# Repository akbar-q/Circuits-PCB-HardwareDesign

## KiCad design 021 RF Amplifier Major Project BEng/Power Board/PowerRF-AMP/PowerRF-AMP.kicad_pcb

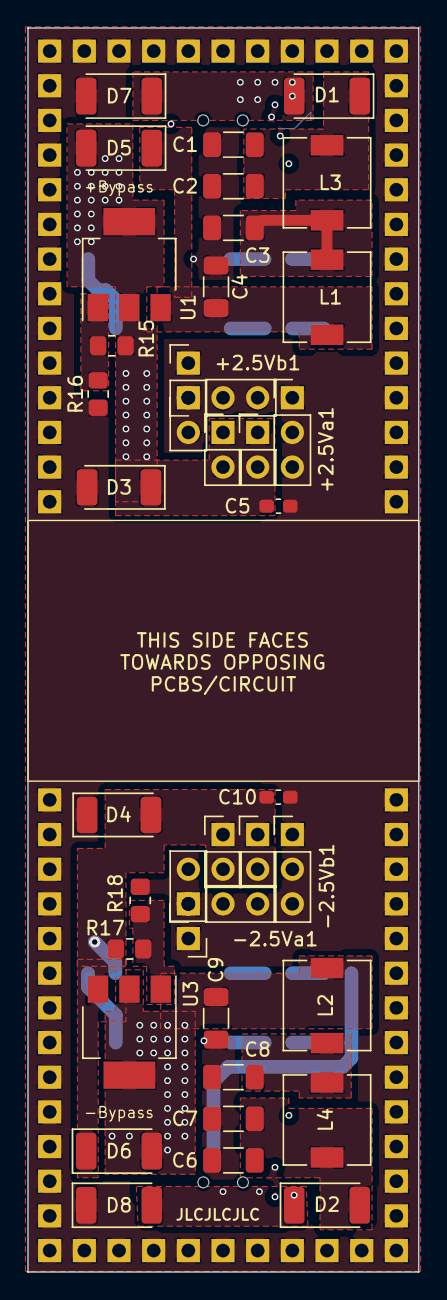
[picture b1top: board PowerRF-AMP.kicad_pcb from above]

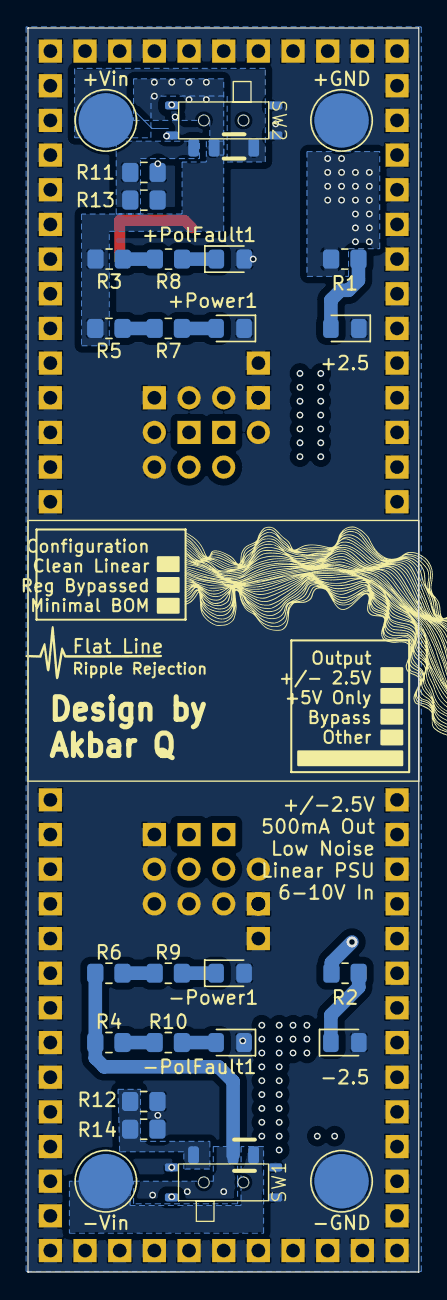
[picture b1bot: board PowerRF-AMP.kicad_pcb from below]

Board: 4 copper layers, 28.6 x 91.1 mm, 64 parts (26 on the bottom side), 27 nets.

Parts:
+2.5: LED; LED_0805_2012Metric_Pad1.15x1.40mm_HandSolder
+2.5Va1, +2.5Vb1: Conn_01x02_Pin; PinHeader_1x02_P2.54mm_Vertical
+G1, +G2, +G3: Conn_01x03; PinHeader_1x03_P2.54mm_Vertical
+GND: TestPoint; TestPoint_Pad_D4.0mm
+PolFault1: LED; LED_0805_2012Metric_Pad1.15x1.40mm_HandSolder
+Power1: LED; LED_0805_2012Metric_Pad1.15x1.40mm_HandSolder
+Vin: TestPoint; TestPoint_Pad_D4.0mm
-2.5: LED; LED_0805_2012Metric_Pad1.15x1.40mm_HandSolder
-2.5Va1, -2.5Vb1: Conn_01x02_Pin; PinHeader_1x02_P2.54mm_Vertical
-G1, -G2, -G3: Conn_01x03; PinHeader_1x03_P2.54mm_Vertical
-GND: TestPoint; TestPoint_Pad_D4.0mm
-PolFault1: LED; LED_0805_2012Metric_Pad1.15x1.40mm_HandSolder
-Power1: LED; LED_0805_2012Metric_Pad1.15x1.40mm_HandSolder
-Vin: TestPoint; TestPoint_Pad_D4.0mm
C1, C2, C3, C4, C6, C7, C8, C9: 2.2u; C_1206_3216Metric_Pad1.33x1.80mm_HandSolder
C5, C10: 100n; C_0603_1608Metric_Pad1.08x0.95mm_HandSolder
D1, D2: Diode; D_MELF
D3, D4: D_Zener; D_2010_5025Metric_Pad1.52x2.65mm_HandSolder
D5, D6: Bypass; D_MELF
D7, D8: PolFaultClamp-DNP; D_MELF
L1, L2, L3, L4: L; L_6.3x6.3_H3
R1, R2, R3, R4, R5, R6, R7, R8, R9, R10, R11, R12, R13, R14, R15, R16, R17, R18: 680R; R_0805_2012Metric_Pad1.20x1.40mm_HandSolder
SW1, SW2: SW_SPDT; SPDT-Long-SMD
U1: LM317_SOT-223; SOT-223-3_TabPin2
U3: LM337_SOT223; SOT-223-3_TabPin2

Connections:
GND: +2.5.1 (K), +G1.1, +G1.2, +G1.3, +G2.1, +G2.2, +G2.3, +G3.1, +G3.2, +G3.3, +GND.1, +PolFault1.2 (A), +Power1.1 (K), -2.5.2 (A), -G1.1, -G1.2, -G1.3, -G2.1, -G2.2, -G2.3, -G3.1, -G3.2, -G3.3, -GND.1, -PolFault1.1 (K), -Power1.2 (A), C1.2, C2.2, C3.2, C4.2, C5.2, C6.2, C7.2, C8.2, C9.2, C10.2, D3.2 (A), D4.1 (K), D7.2 (A), D8.1 (K), R11.2, R12.2, R13.2, R14.2, R16.1, R18.1, SW1.0, SW2.0
unnamed: +2.5.2 (A), R1.2
unnamed: +2.5Va1.1, +2.5Va1.2, +2.5Vb1.1, +2.5Vb1.2, C5.1, D3.1 (K), D5.2 (A), R1.1, R15.2, U1.2 (VO)
unnamed: +PolFault1.1 (K), R8.1
unnamed: +Power1.2 (A), R7.1
unnamed: -2.5.1 (K), R2.2
unnamed: -2.5Va1.1, -2.5Va1.2, -2.5Vb1.1, -2.5Vb1.2, C10.1, D4.2 (A), D6.1 (K), R2.1, R17.2, U3.3 (VO)
unnamed: -PolFault1.2 (A), R10.1
unnamed: -Power1.1 (K), R9.1
unnamed: C3.1, L1.1, L3.2
unnamed: C8.1, L2.1, L4.2
unnamed: D1.2 (A), D7.1 (K), R3.2, R5.2, SW2.2 (B)
unnamed: C1.1, C2.1, D1.1 (K), L3.1
unnamed: C6.1, C7.1, D2.2 (A), L4.1
unnamed: D2.1 (K), D8.2 (A), R4.2, R6.2, SW1.2 (B)
unnamed: C4.1, D5.1 (K), L1.2, U1.3 (VI)
unnamed: C9.1, D6.2 (A), L2.2, U3.2 (VI)
unnamed: R3.1, R8.2
unnamed: R5.1, R7.2
unnamed: R6.1, R9.2
unnamed: R4.1, R10.2
unnamed: R12.1, R14.1, SW1.1 (A)
unnamed: -Vin.1, SW1.3 (C)
unnamed: +Vin.1, SW2.1 (A)
unnamed: R11.1, R13.1, SW2.3 (C)
unnamed: R15.1, R16.2, U1.1 (ADJ)
unnamed: R17.1, R18.2, U3.1 (ADJ)

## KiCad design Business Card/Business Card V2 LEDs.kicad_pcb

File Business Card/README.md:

## ADD QR CODES TO CONTACT BASED ON WEBSITE REDACTED INFORMATION AND WEBLINK

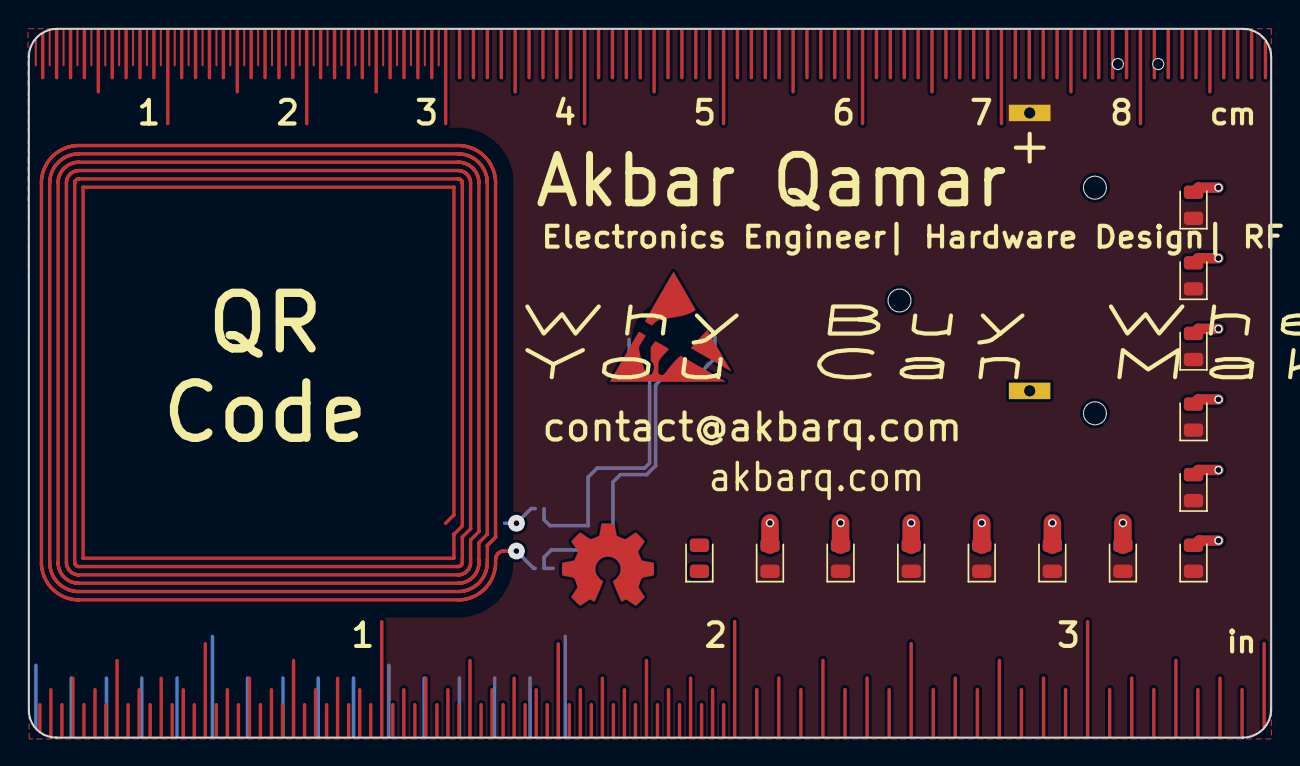
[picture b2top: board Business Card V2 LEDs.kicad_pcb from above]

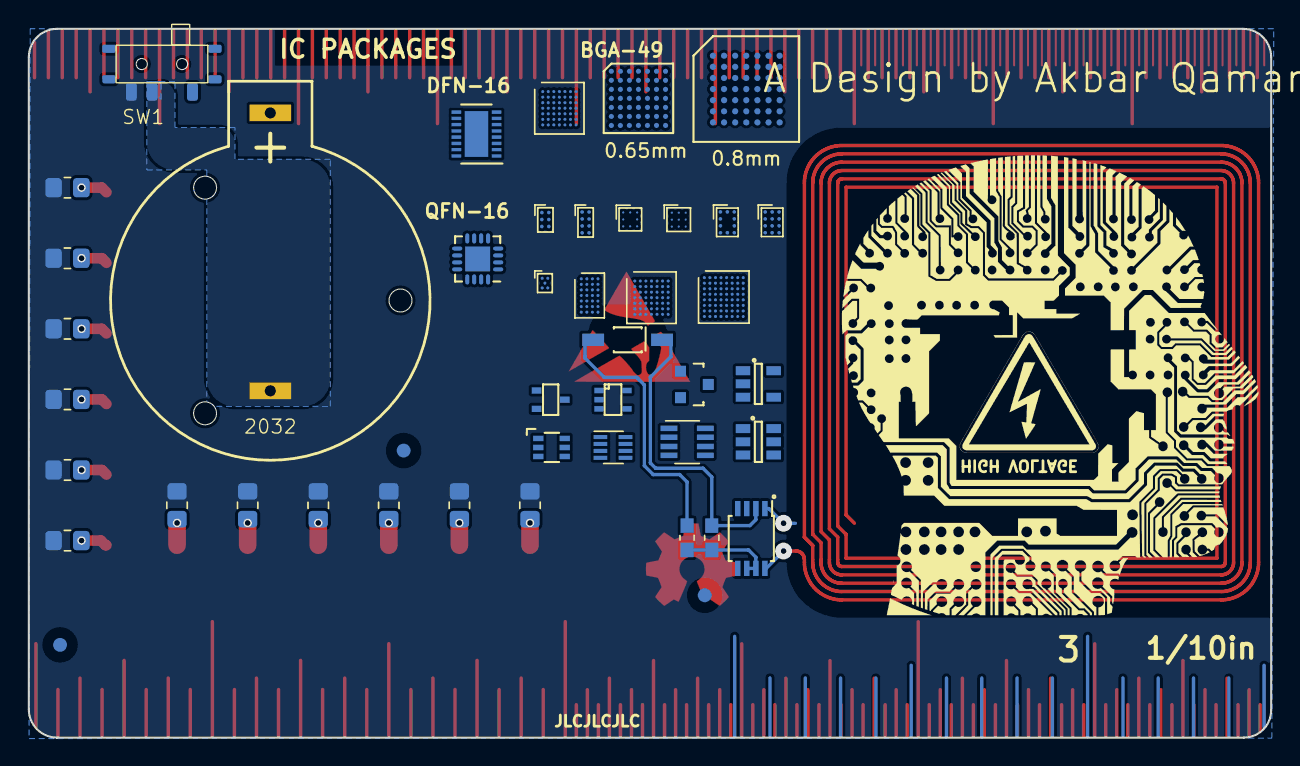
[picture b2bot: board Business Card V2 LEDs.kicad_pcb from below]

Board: 2 copper layers, 89.4 x 51.0 mm, 47 parts (34 on the bottom side), 15 nets.

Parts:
0.4mm: asd; Texas_DSBGA-49_3.33x3.488mm_Layout7x7_P0.4mm
3x3mm: QFN-16-1EP_3x3mm_Pitch0.5mm
3x4mm: DFN-16-1EP_3x4mm_Pitch0.45mm
5: SC-70-5
5#2: SOT-23-5
6: SC-70-6
6#2: SOT-23-6
(0.4mm): Texas_DSBGA-5_0.822x1.116mm_Layout2x1x2_P0.4mm
(0.5mm): Texas_DSBGA-6_0.9x1.4mm_Layout2x3_P0.5mm
BGA-49: BGA_49; BGA_49-0.8mm-7x7mm
BGA-49#2: BGA_49; BGA-49_CSBGA-49_0.65mm
BT1: Battery_Cell; CR2032Holder
C: C_0603_1608Metric_Pad1.05x0.95mm_HandSolder
D1, D2, D3, D4, D5, D6, D7, D8, D9, D10, D11, D12, D13: LED; LED_0805_2012Metric
DSBGA: Texas_DSBGA-8_0.9x1.9mm_Layout2x4_P0.5mm
DSBGA#2: Texas_DSBGA-28_1.9x3.0mm_Layout4x7_P0.4mm
G : LOGO
R: R_0603_1608Metric_Pad1.05x0.95mm_HandSolder
R2, R3, R4, R5, R6, R7, R8, R9, R10, R11, R12, R13: R; R_0805_2012Metric_Pad1.20x1.40mm_HandSolder
SC-70: SC-70
SOT-23: SOT-23
SW1: SW_SPDT; SPDT-Long-SMD
sc-70: SC-70-8
sot-23: TSOT-23-8

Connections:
+3V3: R2.1, R3.1, R4.1, R5.1, R6.1, R7.1, R8.1, R9.1, R10.1, R11.1, R12.1, R13.1, SW1.3 (C)
GND: BT1.2 (-), D2.1 (K), D3.1 (K), D4.1 (K), D5.1 (K), D6.1 (K), D7.1 (K), D8.1 (K), D9.1 (K), D10.1 (K), D11.1 (K), D12.1 (K), D13.1 (K)
unnamed: BT1.1 (+), SW1.2 (B)
unnamed: D2.2 (A), R2.2
unnamed: D3.2 (A), R3.2
unnamed: D4.2 (A), R4.2
unnamed: D5.2 (A), R5.2
unnamed: D6.2 (A), R6.2
unnamed: D7.2 (A), R7.2
unnamed: D8.2 (A), R8.2
unnamed: D9.2 (A), R9.2
unnamed: D10.2 (A), R10.2
unnamed: D11.2 (A), R11.2
unnamed: D12.2 (A), R12.2
unnamed: D13.2 (A), R13.2
